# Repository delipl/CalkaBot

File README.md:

# CalkaBot

CalkaBots are robots created by Jakub Kuziemski and Jakub Delicat. The first one CałkaBot 1.0 was made in 2018 for miniSUMO competition in UTP in Bydgoszcz. We were first grade students then, and we weren't experienced enough, so it was a huge surprise when we got to a semifinal group. The second one, CałkaBot 2.0, was made the following year and won a special prize in Bydgoszcz. We have been appreciated for the progress and for a PCB board project made by Deli. With both robots, improved to versions 1.1 and 2.1, we have gone to Baltic Robo Battles, to face up univeristy students. We weren't surprised when we have lost most of the battles, but CałkaBots were hard opponent many times. We have even managed to win some of the battles against students of technical universities.

# Our Team
- [Jakub Kuziemski (@JakubKivi)](https://github.com/JakubKivi)
- [Jakub Delicat (@delipl)](https://github.com/delipl)
- [Adam Wieczarek (@AWieczarek)](https://github.com/AWieczarek)

CałkaBots 3d0 and 3k0 are comming.

# Software
07.11.2020
We grow up!
It is time for STM32.

# PCB Design
## Features
|Feature|Quantity|
|-------|--------|
|Distans Sensors| 6 |
|Floor Sensors| 4 |
|Accel & Gyro| 1 |
|LiPol charger| 3 |
|LiPol overcharge/overdischarge protection| 3|
|Short Protection| 3 |
|Step down converter 5V| 1 |
|Step down converter 3.3V| 1 |
|Battery voltage checker| 1 |
|Motor drivers| 2 |
|Reset button| 1 |
|Start button| 1 |
|LCD display| 1 |
|3 bit switch| 1 |
|On/Off switch| 1 |
|Optical encoder| 1 |

# Hardware and software tips
To run STM32CubeProgrammer on linux it is nessesery to install java zulu

Ahh.. To run EAGLE on linux it is nessesery to copy library to $EAGLE/lib folder 
`sudo cp /usr/lib/x86_64-linux-gnu/libxcb-dri3.so.0 lib/
`

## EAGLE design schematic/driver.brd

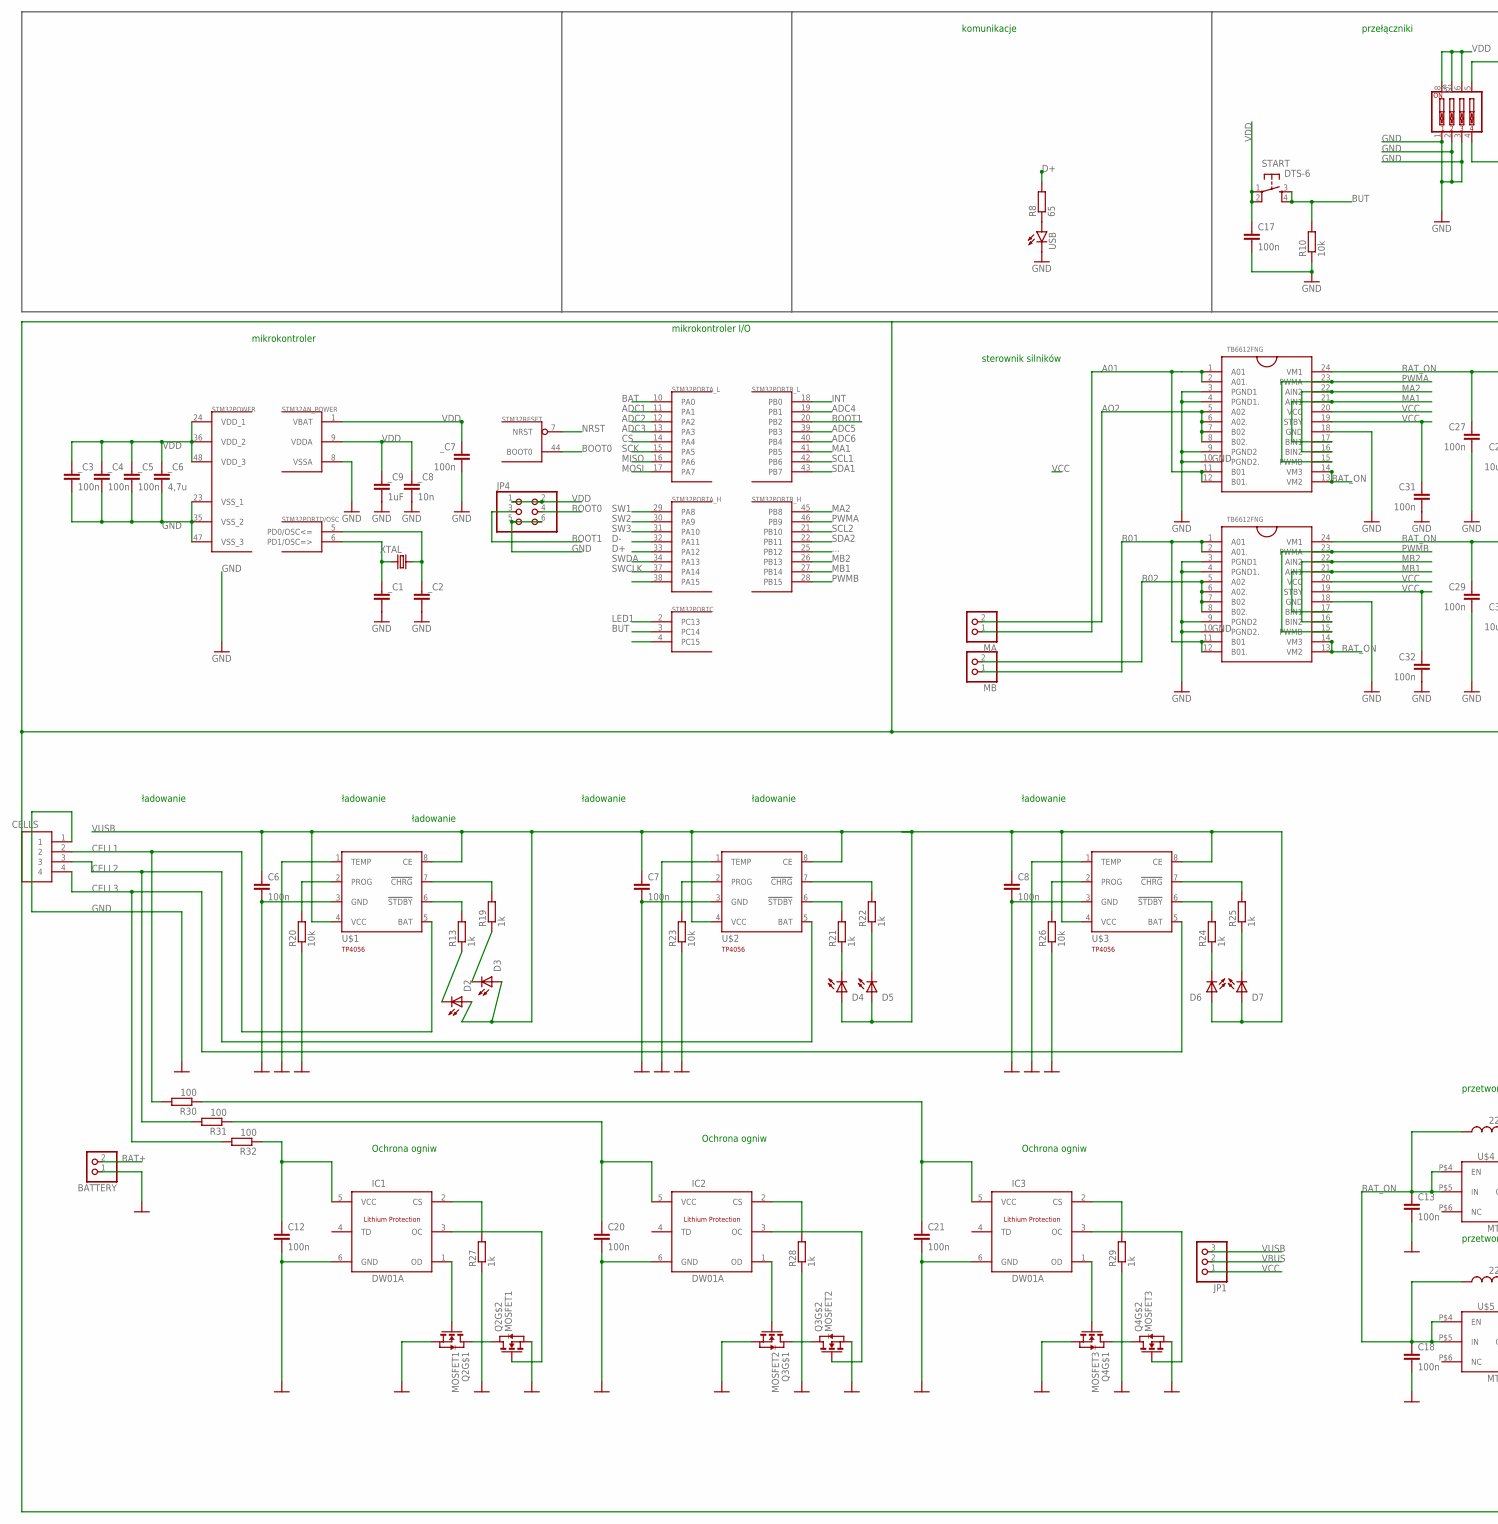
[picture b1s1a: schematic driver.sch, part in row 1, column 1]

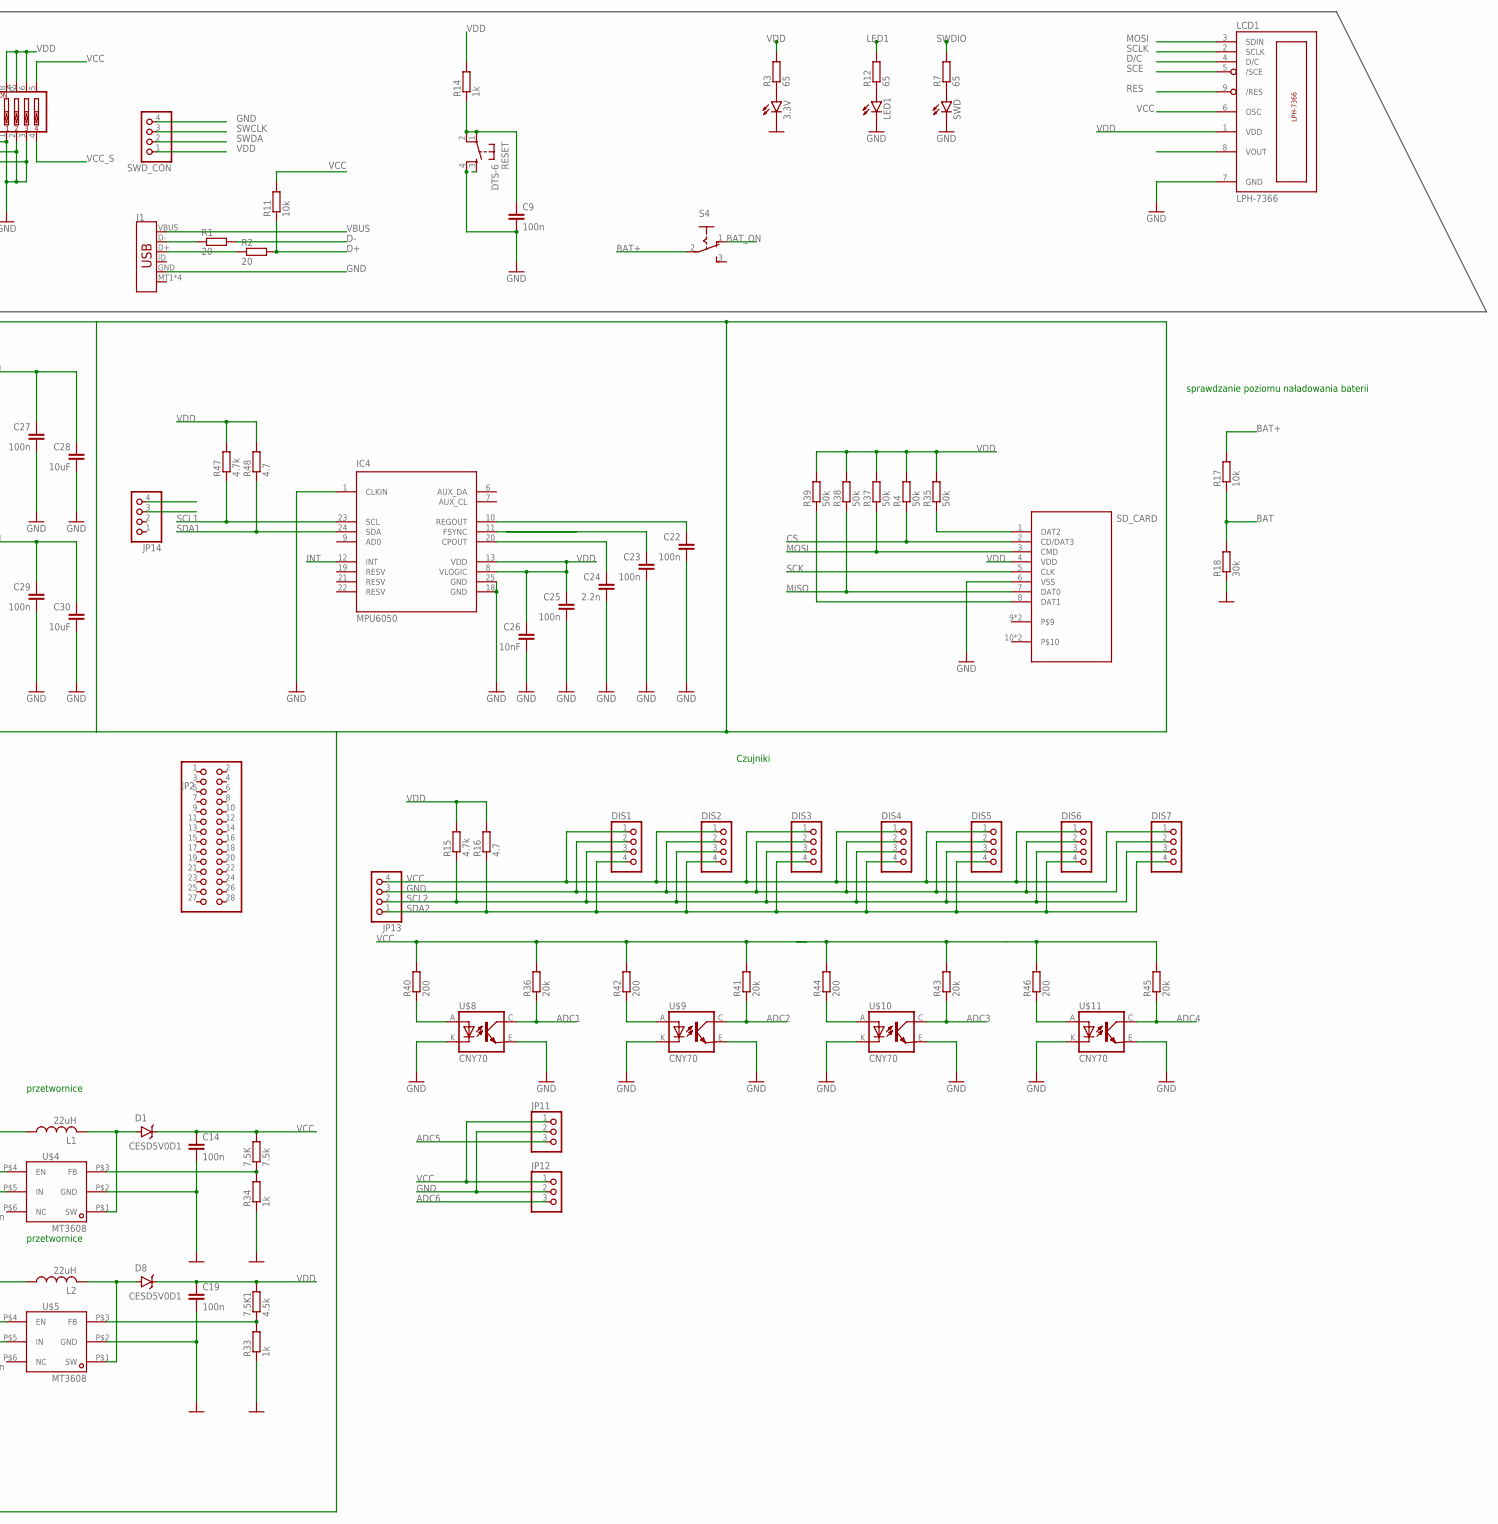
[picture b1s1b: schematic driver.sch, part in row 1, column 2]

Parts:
3.3V: LEDCHIPLED_0805; CHIPLED_0805
7.5K: 7.5k; R0805
7.5K1: 4.5k; R0805
BATTERY: PINHD-1X2; 1X02
C6, C7, C8, C9, C12, C13, C14, C17, C18, C19, C20, C21, C22, C23, C25, C27, C29, C31, C32: 100n; C0603
C24: 2.2n; C0603
C26: 10nF; C0603
C28, C30: 10uF; C0603
CELLS: S4B-XH-A(LF)(SN); HDR-04/RA
D1, D8: CESD5V0D1; SOD-123
D2, D3, D4, D5, D6, D7: LEDCHIPLED-0603-TTW; CHIPLED-0603-TTW
DIS1, DIS2, DIS3, DIS4, DIS5, DIS6, DIS7: PINHD-1X4; 1X04
IC1, IC2, IC3: DW01A; SOT23-6
IC4: MPU6050; QFN50P400X400X95-25T265X275N
J1: USB_MICRO-B_SMT; USB-MICROB
JP1, JP11, JP12: PINHD-1X3; 1X03
JP2: PINHD-2X14; 2X14
JP4: PINHD-2X3; 2X03
JP13, JP14: PINHD-1X4; 1X04
L1, L2: 22uH; L1812
LCD1: LPH-7366
LED1: LEDCHIPLED_0805; CHIPLED_0805
MA: PINHD-1X2/90; 1X02/90
MB: PINHD-1X2/90; 1X02/90
Q2: MOSFET1; SOT363
Q3: MOSFET2; SOT363
Q4: MOSFET3; SOT363
R1, R2: 20; R0805
R3, R7, R8, R12: 65; R0805
R4, R35, R37, R38, R39: 50k; R0805
R10, R11, R17, R20, R23, R26: 10k; R0805
R13, R14, R19, R21, R22, R24, R25, R27, R28, R29, R33, R34: 1k; R0805
R15, R47: 4.7k; R0805
R16, R48: 4.7; R0805
R18: 30k; R0805
R30, R31, R32: 100; R0805
R36, R41, R43, R45: 20k; R0805
R40, R42, R44, R46: 200; R0805
RESET: DTS-6
S2: SW_DIP-4; EDG-04
S4: 255SB
SD_CARD: 693071010811
START: DTS-6
STM32: STM32F10XCXT6; TQFP48
SWD: LEDCHIPLED_0805; CHIPLED_0805
SWD_CON: PINHD-1X4; 1X04
U$1, U$2, U$3: TP4056; SOT23-8
U$4, U$5: MT3608SOT23-6; SOT23-6
U$6, U$7: TB6612FNG; SSOP24
U$8, U$9, U$10, U$11: CNY70; 4
USB: LEDCHIPLED_0805; CHIPLED_0805
XTAL: KX-7; 3.2X2.5_KX-7
_C1, _C2: C-EUC0603; C0603
_C3, _C4, _C5, _C7: 100n; C0603
_C6: 4,7u; C0603
_C8: 10n; C0603
_C9: 1uF; C0603

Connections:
...: STM32.25 (PB12)
A01: MA.1, U$6.1 (A01), U$6.2 (A01.), U$6.11 (B01), U$6.12 (B01.)
ADC1: R36.1, STM32.11 (PA1), U$8.C (COL)
ADC2: R41.1, STM32.12 (PA2), U$9.C (COL)
ADC3: R43.1, STM32.13 (PA3), U$10.C (COL)
ADC4: R45.1, STM32.19 (PB1), U$11.C (COL)
ADC5: JP11.3, STM32.39 (PB3)
ADC6: JP12.3, STM32.40 (PB4)
AO2: MA.2, U$6.5 (A02), U$6.6 (A02.), U$6.7 (B02), U$6.8 (B02.)
B01: MB.1, U$7.1 (A01), U$7.2 (A01.), U$7.11 (B01), U$7.12 (B01.)
B02: MB.2, U$7.5 (A02), U$7.6 (A02.), U$7.7 (B02), U$7.8 (B02.)
BAT: R17.1, R18.2, STM32.10 (PA0)
BAT+: BATTERY.2, R17.2, S4.2
BAT_ON: C13.1, C18.1, C27.1, C28.1, C29.1, C30.1, L1.1, L2.1, S4.1 (O), U$4.P$4 (EN), U$4.P$5 (IN), U$5.P$4 (EN), U$5.P$5 (IN), U$6.13 (VM2), U$6.14 (VM3), U$6.24 (VM1), U$7.13 (VM2), U$7.14 (VM3), U$7.24 (VM1)
BOOT0: JP4.4, STM32.44 (BOOT0)
BOOT1: JP4.3, STM32.20 (PB2)
BUT: R10.2, START.3, START.4, STM32.3 (PC14)
CELL1: CELLS.2, R30.2, U$1.5 (BAT)
CELL2: CELLS.3, R31.2, U$2.5 (BAT)
CELL3: CELLS.4, R32.2, U$3.5 (BAT)
CS: R4.1, SD_CARD.2 (CD/DAT3), STM32.14 (PA4)
D+: R2.2, R8.2, R11.1, STM32.33 (PA12)
D-: R1.2, STM32.32 (PA11)
D/C: LCD1.4 (D/C)
GND: 3.3V.C, BATTERY.1, C6.2, C7.2, C8.2, C9.2, C12.2, C13.2, C14.2, C17.2, C18.2, C19.2, C20.2, C21.2, C22.2, C23.2, C24.2, C25.2, C26.2, C27.2, C28.2, C29.2, C30.2, C31.2, C32.2, CELLS.1, DIS1.2, DIS2.2, DIS3.2, DIS4.2, DIS5.2, DIS6.2, DIS7.2, IC1.6 (GND), IC2.6 (GND), IC3.6 (GND), IC4.1 (CLKIN), IC4.18 (GND), IC4.25 (GND), J1.GND, JP4.5, JP4.6, JP11.2, JP12.2, JP13.3, LCD1.7 (GND), LED1.C, Q2.1 (S), Q2.4 (S), Q3.1 (S), Q3.4 (S), Q4.1 (S), Q4.4 (S), R10.1, R18.1, R20.1, R23.1, R26.1, R27.1, R28.1, R29.1, R33.1, R34.1, RESET.4, S2.1, S2.2, S2.3, SD_CARD.6 (VSS), STM32.8 (VSSA), STM32.23 (VSS_1), STM32.35 (VSS_2), STM32.47 (VSS_3), SWD.C, SWD_CON.4, U$1.1 (TEMP), U$1.3 (GND), U$2.1 (TEMP), U$2.3 (GND), U$3.1 (TEMP), U$3.3 (GND), U$4.P$2 (GND), U$5.P$2 (GND), U$6.3 (PGND1), U$6.4 (PGND1.), U$6.9 (PGND2), U$6.10 (PGND2.), U$6.18 (GND), U$7.3 (PGND1), U$7.4 (PGND1.), U$7.9 (PGND2), U$7.10 (PGND2.), U$7.18 (GND), U$8.E (EMI), U$8.K (C), U$9.E (EMI), U$9.K (C), U$10.E (EMI), U$10.K (C), U$11.E (EMI), U$11.K (C), USB.C, _C1.2, _C2.2, _C3.2, _C4.2, _C5.2, _C6.2, _C7.2, _C8.2, _C9.2
INT: IC4.12 (INT), STM32.18 (PB0)
LED1: R12.2, STM32.2 (PC13)
MA1: STM32.41 (PB5), U$6.17 (BIN1), U$6.21 (AIN1)
MA2: STM32.45 (PB8), U$6.16 (BIN2), U$6.22 (AIN2)
MB1: STM32.27 (PB14), U$7.17 (BIN1), U$7.21 (AIN1)
MB2: STM32.26 (PB13), U$7.16 (BIN2), U$7.22 (AIN2)
MISO: R38.1, SD_CARD.7 (DAT0), STM32.16 (PA6)
MOSI: LCD1.3 (SDIN), R37.1, SD_CARD.3 (CMD), STM32.17 (PA7)
unnamed: R40.1, U$8.A
unnamed: STM32.5 (PD0/OSC<=), XTAL.1, _C2.1
unnamed: STM32.6 (PD1/OSC=>), XTAL.3 (2), _C1.1
unnamed: J1.D+, R2.1
unnamed: J1.D-, R1.1
unnamed: R22.2, U$2.7 (!CHRG)
unnamed: R13.2, U$1.6 (!STDBY)
unnamed: 3.3V.A, R3.1
unnamed: R7.1, SWD.A
unnamed: D2.C@1 (C), R13.1
unnamed: R19.2, U$1.7 (!CHRG)
unnamed: D3.C@1 (C), R19.1
unnamed: R20.2, U$1.2 (PROG)
unnamed: R21.2, U$2.6 (!STDBY)
unnamed: D4.C@1 (C), R21.1
unnamed: D5.C@1 (C), R22.1
unnamed: R23.2, U$2.2 (PROG)
unnamed: R25.2, U$3.7 (!CHRG)
unnamed: R24.2, U$3.6 (!STDBY)
unnamed: D6.C@1 (C), R24.1
unnamed: D7.C@1 (C), R25.1
unnamed: R26.2, U$3.2 (PROG)
unnamed: IC1.1 (OD), Q2.2 (G)
unnamed: IC1.3 (OC), Q2.5 (G)
unnamed: C12.1, IC1.5 (VCC), R32.1
unnamed: IC1.2 (CS), R27.2
unnamed: Q2.3 (D), Q2.6 (D)
unnamed: IC2.2 (CS), R28.2
unnamed: C20.1, IC2.5 (VCC), R31.1
unnamed: IC2.1 (OD), Q3.2 (G)
unnamed: IC2.3 (OC), Q3.5 (G)
unnamed: Q3.3 (D), Q3.6 (D)
unnamed: IC3.2 (CS), R29.2
unnamed: C21.1, IC3.5 (VCC), R30.1
unnamed: IC3.1 (OD), Q4.2 (G)
unnamed: IC3.3 (OC), Q4.5 (G)
unnamed: Q4.3 (D), Q4.6 (D)
unnamed: C22.1, IC4.10 (REGOUT)
unnamed: C24.1, IC4.20 (CPOUT)
unnamed: D1.A, L1.2, U$4.P$1 (SW)
unnamed: D8.A, L2.2, U$5.P$1 (SW)
unnamed: 7.5K1.1, R33.2, U$5.P$3 (FB)
unnamed: 7.5K.1, R34.2, U$4.P$3 (FB)
unnamed: LED1.A, R12.1
unnamed: R8.1, USB.A
unnamed: R42.1, U$9.A
unnamed: R35.1, SD_CARD.1 (DAT2)
unnamed: R44.1, U$10.A
unnamed: R39.1, SD_CARD.8 (DAT1)
unnamed: R43.2, R44.2
unnamed: R46.1, U$11.A
unnamed: R45.2, R46.2
NRST: C9.1, R14.1, RESET.1, RESET.2, STM32.7 (NRST)
PC15: STM32.4 (PC15)
PWMA: STM32.46 (PB9), U$6.15 (PWMB), U$6.23 (PWMA)
PWMB: STM32.28 (PB15), U$7.15 (PWMB), U$7.23 (PWMA)
RES: LCD1.9 (/RES)
SCE: LCD1.5 (/SCE)
SCK: SD_CARD.5 (CLK), STM32.15 (PA5)
SCL1: IC4.23 (SCL), R47.1, STM32.42 (PB6)
SCL2: DIS1.3, DIS2.3, DIS3.3, DIS4.3, DIS5.3, DIS6.3, DIS7.3, JP13.2, R15.1, STM32.21 (PB10)
SCLK: LCD1.2 (SCLK)
SDA1: IC4.24 (SDA), R48.1, STM32.43 (PB7)
SDA2: DIS1.4, DIS2.4, DIS3.4, DIS4.4, DIS5.4, DIS6.4, DIS7.4, JP13.1, R16.1, STM32.22 (PB11)
SW1: STM32.29 (PA8)
SW2: STM32.30 (PA9)
SW3: STM32.31 (PA10)
SWCLK: STM32.37 (PA14), SWD_CON.3
SWDA: STM32.34 (PA13), SWD_CON.2
SWDIO: R7.2
TDI: STM32.38 (PA15)
VBUS: J1.VBUS, JP1.2
VCC: 7.5K.2, C14.1, C31.1, C32.1, D1.C, DIS1.1, DIS2.1, DIS3.1, DIS4.1, DIS5.1, DIS6.1, DIS7.1, JP1.1, JP11.1, JP12.1, JP13.4, LCD1.6 (OSC), R11.2, R36.2, R40.2, R41.2, R42.2, S2.5, U$6.19 (STBY), U$6.20 (VCC), U$7.19 (STBY), U$7.20 (VCC)
VCC_S: S2.4
VDD: 7.5K1.2, C17.1, C19.1, C25.1, C26.1, D8.C, IC4.8 (VLOGIC), IC4.13 (VDD), JP4.1, JP4.2, LCD1.1 (VDD), R3.2, R4.2, R14.2, R15.2, R16.2, R35.2, R37.2, R38.2, R39.2, R47.2, R48.2, S2.6, S2.7, S2.8, SD_CARD.4 (VDD), START.1, START.2, STM32.1 (VBAT), STM32.9 (VDDA), STM32.24 (VDD_1), STM32.36 (VDD_2), STM32.48 (VDD_3), SWD_CON.1, _C3.1, _C4.1, _C5.1, _C6.1, _C7.1, _C8.1, _C9.1
VUSB: C6.1, C7.1, C8.1, D2.A@1 (A), D3.A@1 (A), D4.A@1 (A), D5.A@1 (A), D6.A@1 (A), D7.A@1 (A), JP1.3, U$1.4 (VCC), U$1.8 (CE), U$2.4 (VCC), U$2.8 (CE), U$3.4 (VCC), U$3.8 (CE)

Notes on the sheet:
komunikacje
przełączniki
mikrokontroler
mikrokontroler I/O
sterownik silników
sprawdzanie poziomu naładowania baterii
ładowanie
Ochrona ogniw
przetwornice
Czujniki

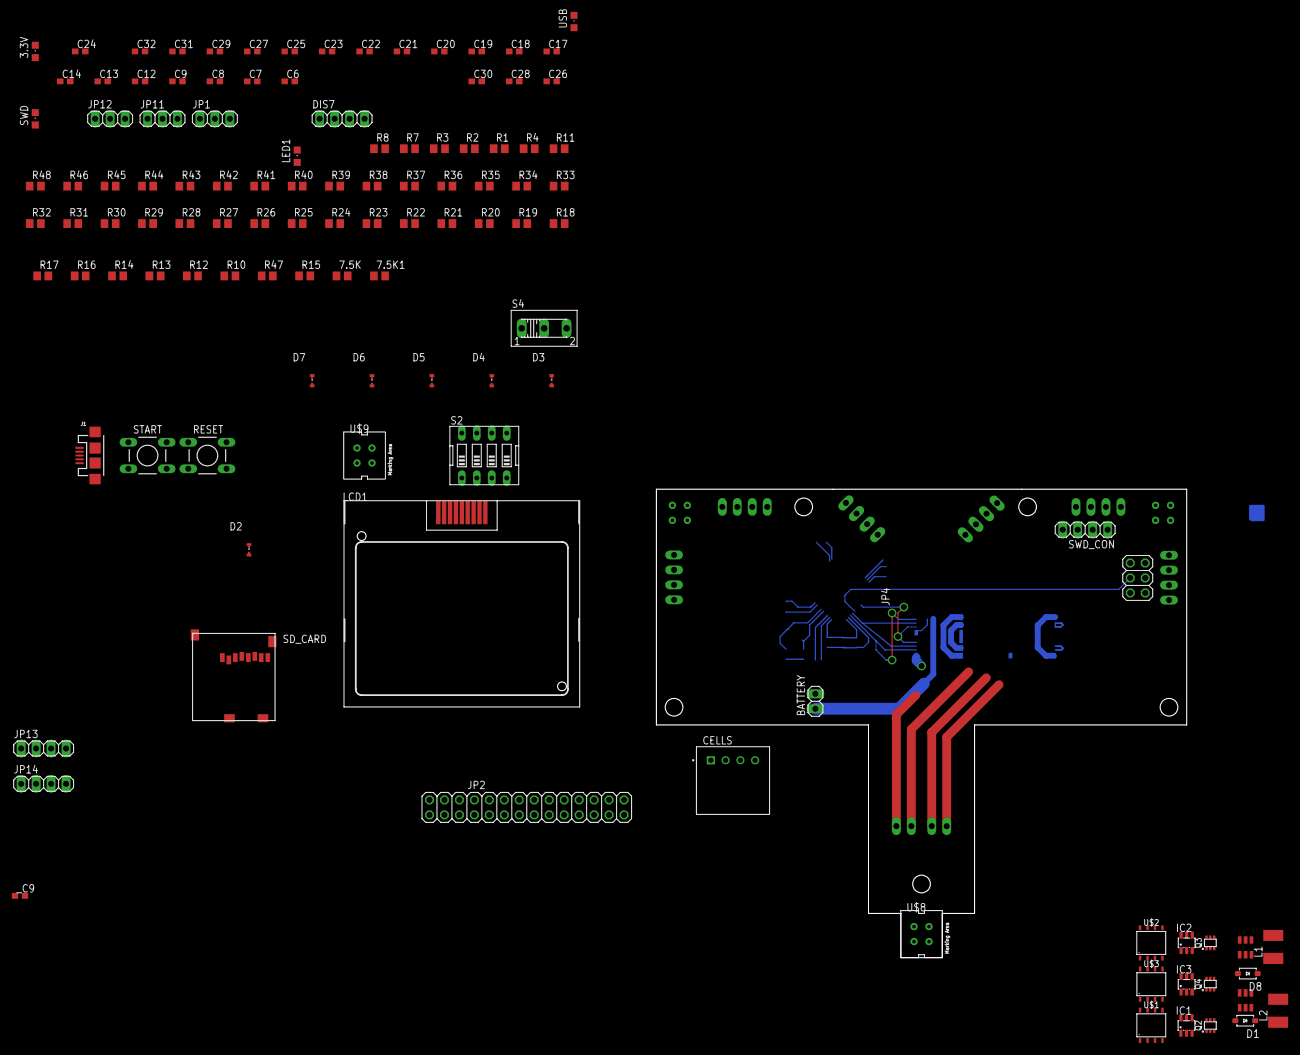
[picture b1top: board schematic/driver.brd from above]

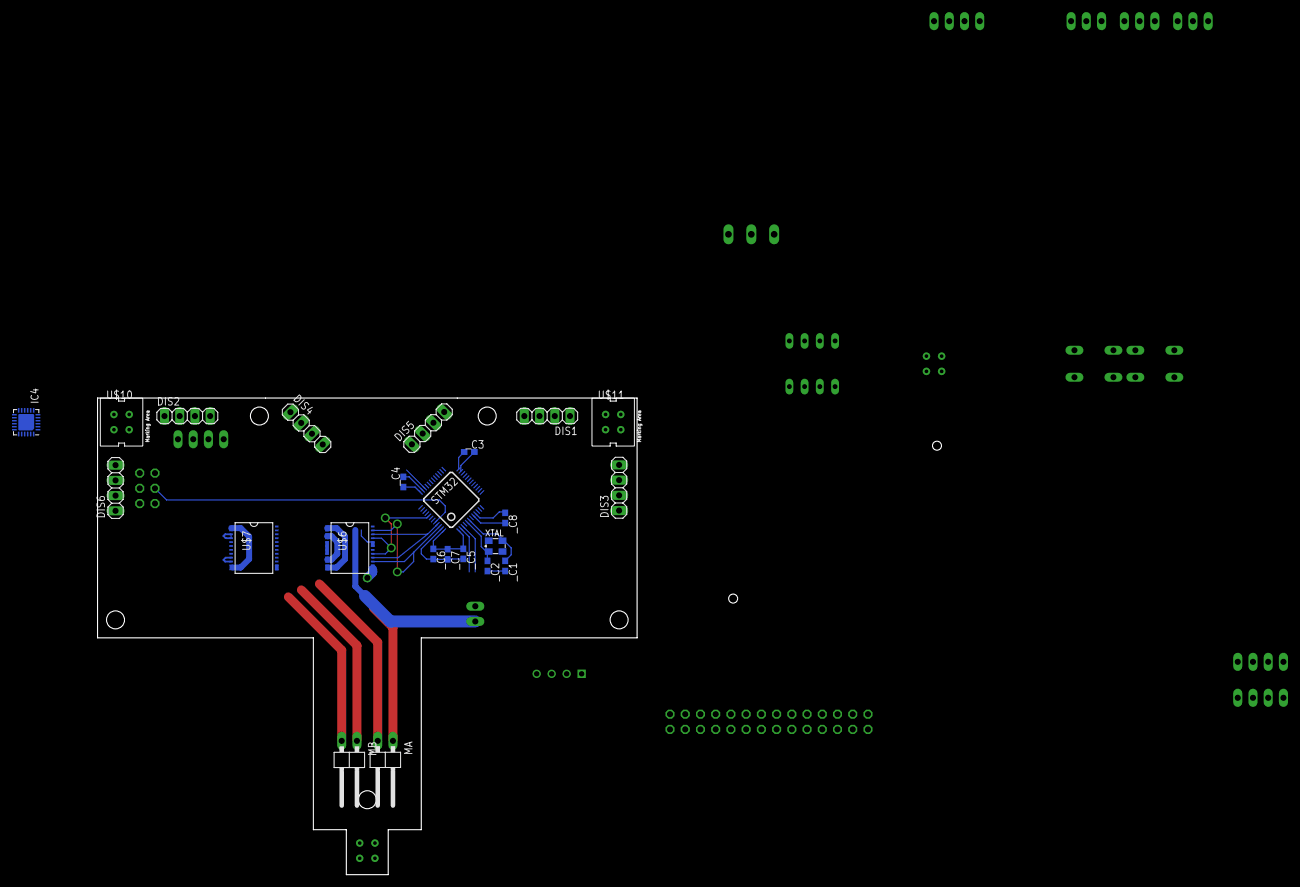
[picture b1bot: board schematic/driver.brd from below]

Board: 2 copper layers, 90.0 x 79.5 mm, 139 parts (23 on the bottom side), 97 nets.

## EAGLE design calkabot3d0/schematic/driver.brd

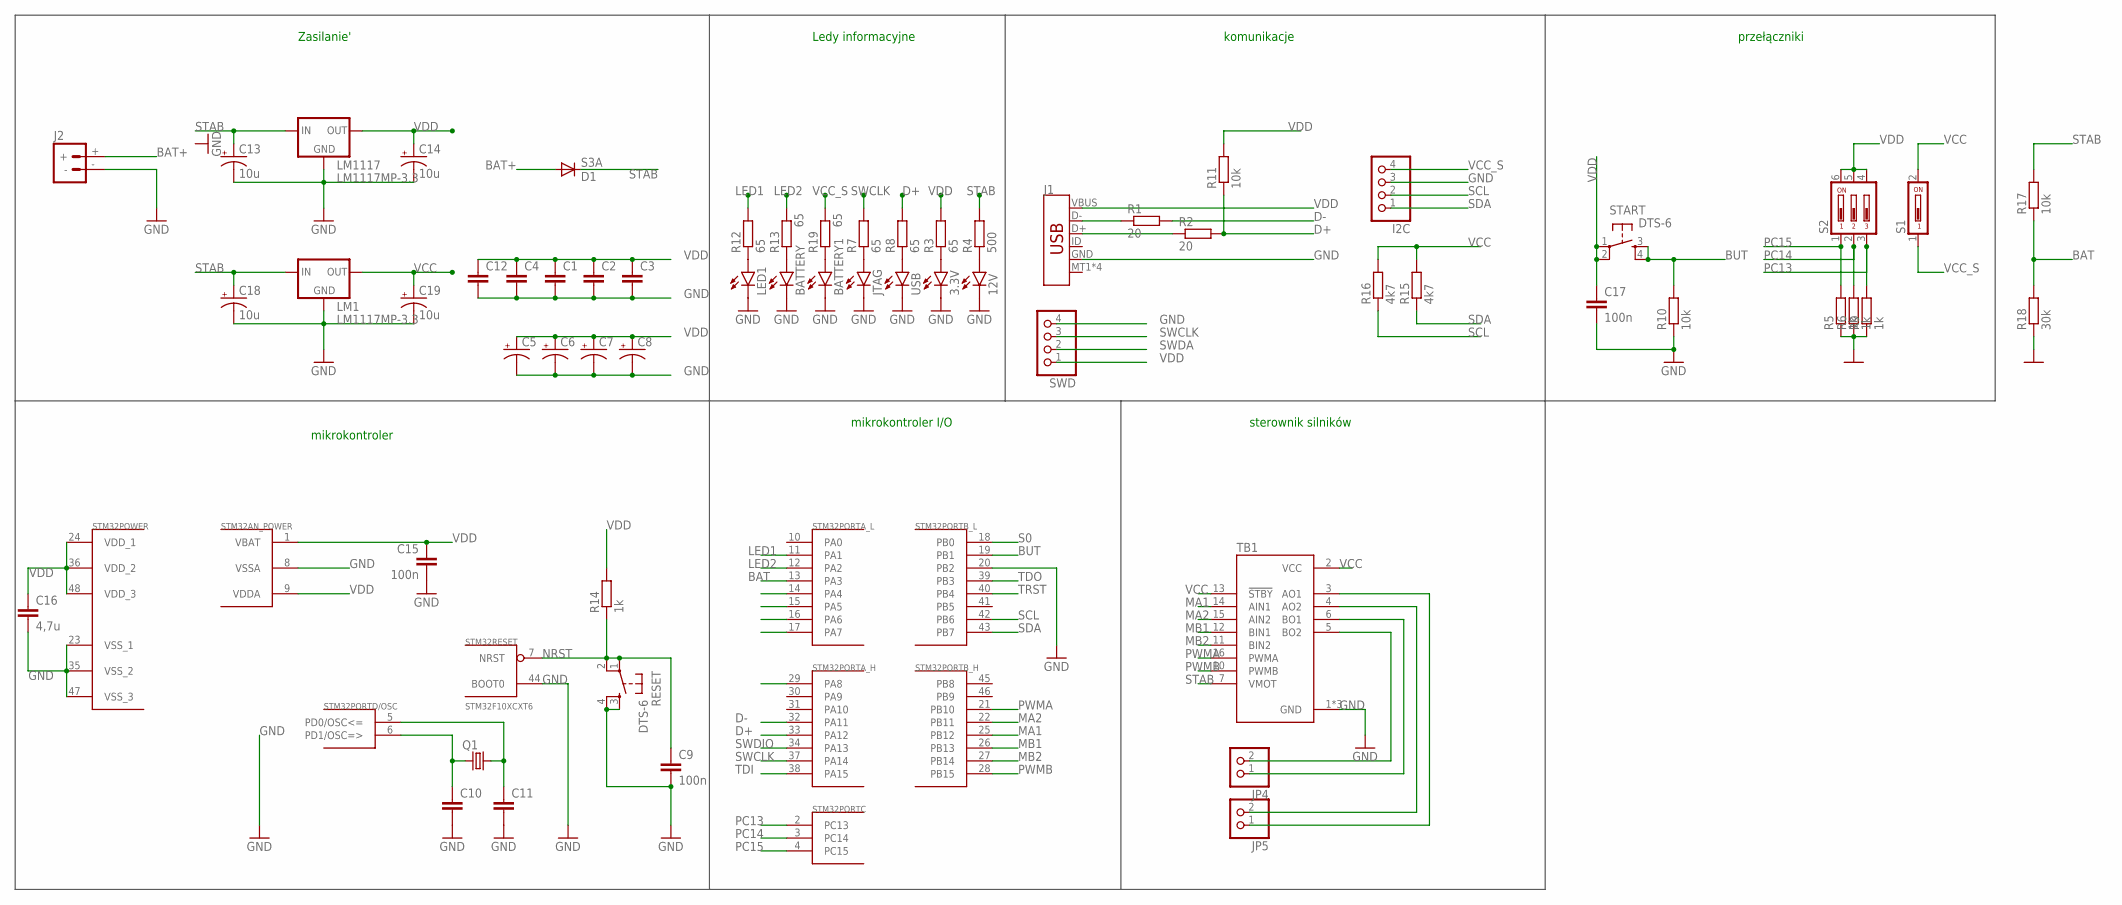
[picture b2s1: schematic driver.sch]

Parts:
3.3V, 12V: LEDCHIPLED_0805; CHIPLED_0805
BATTERY, BATTERY1: LEDCHIPLED_0805; CHIPLED_0805
C1, C2, C3, C4, C10, C11, C12: C-EUC0603; C0603
C5, C6, C7, C8: CPOL-USCT3528; CT3528
C9, C15, C17: 100n; C0603
C13, C14, C18, C19: 10u; CT3528
C16: 4,7u; C0603
D1: S3A; DO214AB
I2C: PINHD-1X4; 1X04
J1: USB_MICRO-B_SMT; USB-MICROB
J2: BATTERY_CONN_DEANS; DEANS
JP4, JP5: PINHD-1X2/90; 1X02/90
JTAG: LEDCHIPLED_0805; CHIPLED_0805
LED1: LEDCHIPLED_0805; CHIPLED_0805
LM1, LM1117: LM1117MP-3.3; SOT223
Q1: KX-7; 3.2X2.5_KX-7
R1, R2: 20; R0805
R3, R7, R8, R12, R13, R19: 65; R0805
R4: 500; R0805
R5, R6, R9, R14: 1k; R0805
R10, R11, R17: 10k; R0805
R15, R16: 4k7; R0805
R18: 30k; R0805
RESET: DTS-6
S1: SD4-01
S2: DP03; DP-03
START: DTS-6
STM32: STM32F10XCXT6; TQFP48
SWD: PINHD-1X4; 1X04
TB1: POLOLU-713; SHIELD_POLOLU-713
USB: LEDCHIPLED_0805; CHIPLED_0805

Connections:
BAT: R17.1, R18.2, STM32.13 (PA3)
BAT+: D1.A, J2.+
BUT: R10.2, START.3, START.4, STM32.19 (PB1)
D+: R2.2, R8.2, R11.1, STM32.33 (PA12)
D-: R1.2, STM32.32 (PA11)
GND: 3.3V.C, 12V.C, BATTERY.C, BATTERY1.C, C1.2, C2.2, C3.2, C4.2, C5.-, C6.-, C7.-, C8.-, C9.2, C10.2, C11.2, C12.2, C13.-, C14.-, C15.2, C16.2, C17.2, C18.-, C19.-, I2C.3, J1.GND, J2.-, JTAG.C, LED1.C, LM1.1 (GND), LM1117.1 (GND), R5.1, R6.1, R9.1, R10.1, R18.1, RESET.3, RESET.4, STM32.8 (VSSA), STM32.20 (PB2), STM32.23 (VSS_1), STM32.35 (VSS_2), STM32.44 (BOOT0), STM32.47 (VSS_3), SWD.4, TB1.1 (GND), TB1.8 (GND), TB1.9 (GND), USB.C
LED1: R12.2, STM32.11 (PA1)
LED2: R13.2, STM32.12 (PA2)
MA1: STM32.25 (PB12), TB1.14 (AIN1)
MA2: STM32.22 (PB11), TB1.15 (AIN2)
MB1: STM32.26 (PB13), TB1.12 (BIN1)
MB2: STM32.27 (PB14), TB1.11 (BIN2)
unnamed: 3.3V.A, R3.1
unnamed: 12V.A, R4.1
unnamed: C11.1, Q1.1, STM32.5 (PD0/OSC<=)
unnamed: C10.1, Q1.3 (2), STM32.6 (PD1/OSC=>)
unnamed: LED1.A, R12.1
unnamed: J1.D+, R2.1
unnamed: J1.D-, R1.1
unnamed: BATTERY.A, R13.1
unnamed: BATTERY1.A, R19.1
unnamed: JTAG.A, R7.1
unnamed: R8.1, USB.A
unnamed: JP4.2, TB1.5 (BO2)
unnamed: JP4.1, TB1.6 (BO1)
unnamed: JP5.2, TB1.4 (AO2)
unnamed: JP5.1, TB1.3 (AO1)
NRST: C9.1, R14.1, RESET.1, RESET.2, STM32.7 (NRST)
PC13: R9.2, S2.3, STM32.2 (PC13)
PC14: R6.2, S2.2, STM32.3 (PC14)
PC15: R5.2, S2.1, STM32.4 (PC15)
PWMA: STM32.21 (PB10), TB1.16 (PWMA)
PWMB: STM32.28 (PB15), TB1.10 (PWMB)
S0: STM32.18 (PB0)
S1: STM32.17 (PA7)
S2: STM32.16 (PA6)
S3: STM32.15 (PA5)
S4: STM32.14 (PA4)
SCL: I2C.2, R16.1, STM32.42 (PB6)
SDA: I2C.1, R15.1, STM32.43 (PB7)
STAB: C13.+, C18.+, D1.C, LM1.3 (IN), LM1117.3 (IN), R4.2, R17.2, TB1.7 (VMOT)
SWCLK: R7.2, STM32.37 (PA14), SWD.3
SWDA: SWD.2
SWDIO: STM32.34 (PA13)
TDI: STM32.38 (PA15)
TDO: STM32.39 (PB3)
TRST: STM32.40 (PB4)
VCC: C19.+, LM1.2 (OUT), LM1.4 (OUT), R15.2, R16.2, S1.2, TB1.2 (VCC), TB1.13 (!STBY)
VCC_S: I2C.4, R19.2, S1.1
VDD: C1.1, C2.1, C3.1, C4.1, C5.+, C6.+, C7.+, C8.+, C12.1, C14.+, C15.1, C16.1, C17.1, J1.VBUS, LM1117.2 (OUT), LM1117.4 (OUT), R3.2, R11.2, R14.2, S2.4, S2.5, S2.6, START.1, START.2, STM32.1 (VBAT), STM32.9 (VDDA), STM32.24 (VDD_1), STM32.36 (VDD_2), STM32.48 (VDD_3), SWD.1

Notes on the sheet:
Zasilanie'
Ledy informacyjne
komunikacje
przełączniki
mikrokontroler
mikrokontroler I/O
sterownik silników

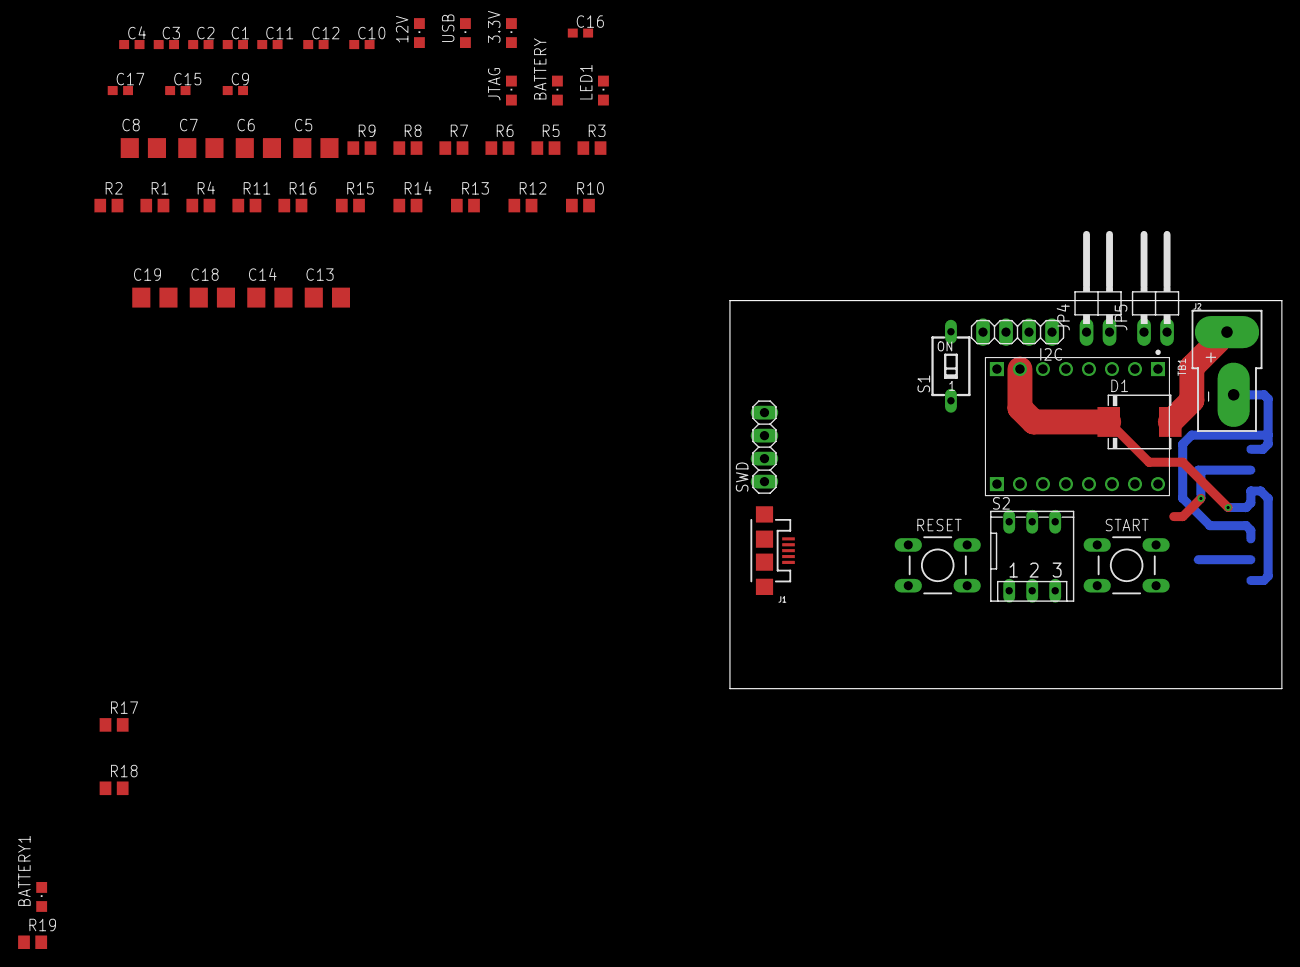
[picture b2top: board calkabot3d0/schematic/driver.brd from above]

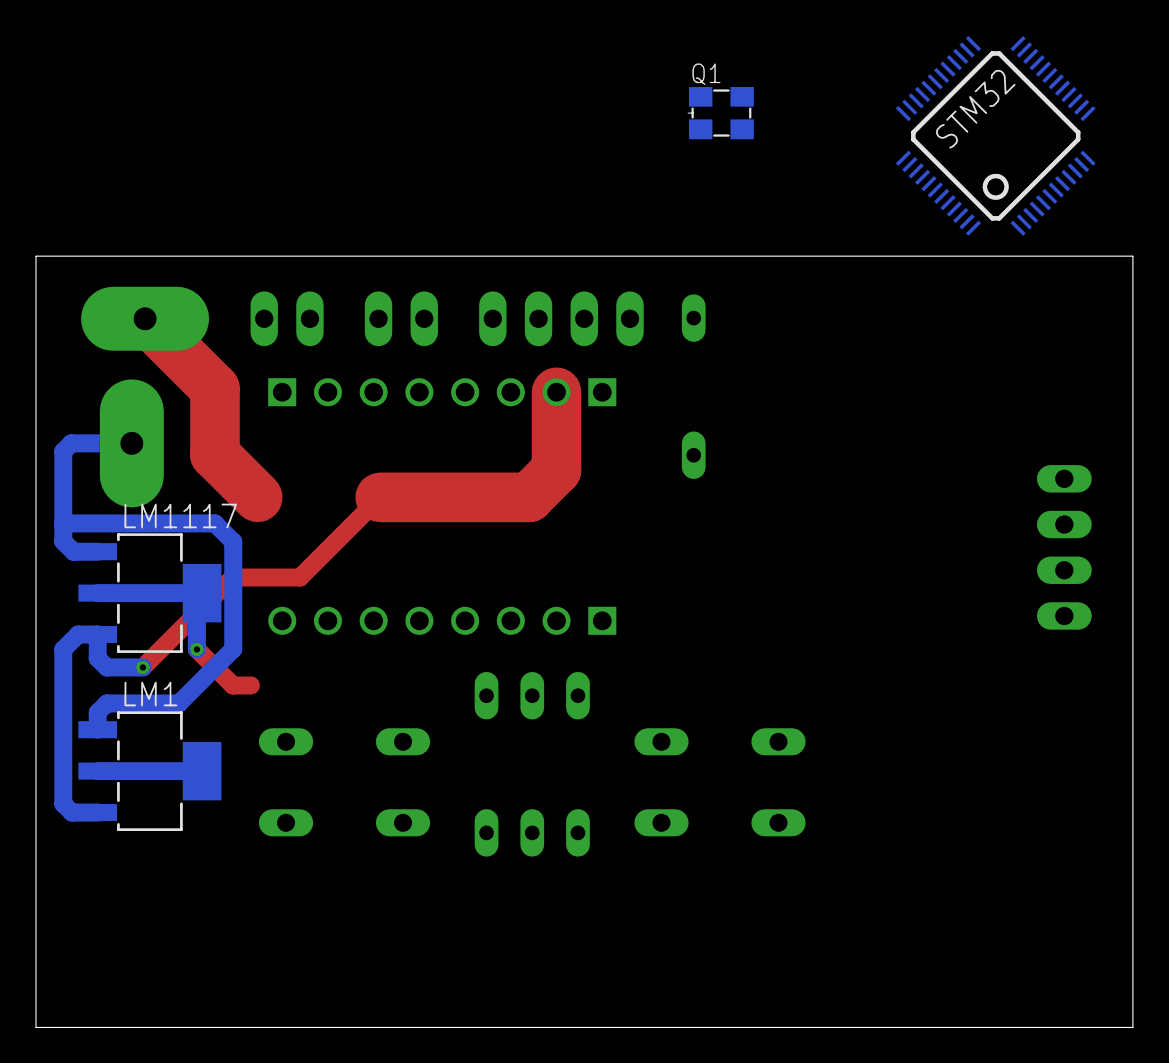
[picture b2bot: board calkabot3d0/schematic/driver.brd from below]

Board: 2 copper layers, 60.9 x 42.9 mm, 61 parts (4 on the bottom side), 40 nets.

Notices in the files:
parts and their libraries:
crystal-geyer_V1_0: Copyright: Geyer-Electronic
SparkFun-Connectors: Licensing: Creative Commons ShareAlike 4.0 International - https://creativecommons.org/licenses/by-sa/4.0
Wurth_Elektronik_Electromechanic_Input-O: Copyright: Würth Elektronik
